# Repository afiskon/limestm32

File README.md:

# limestm32
LimeSTM32: open development board based on STM32F405/STM32F415

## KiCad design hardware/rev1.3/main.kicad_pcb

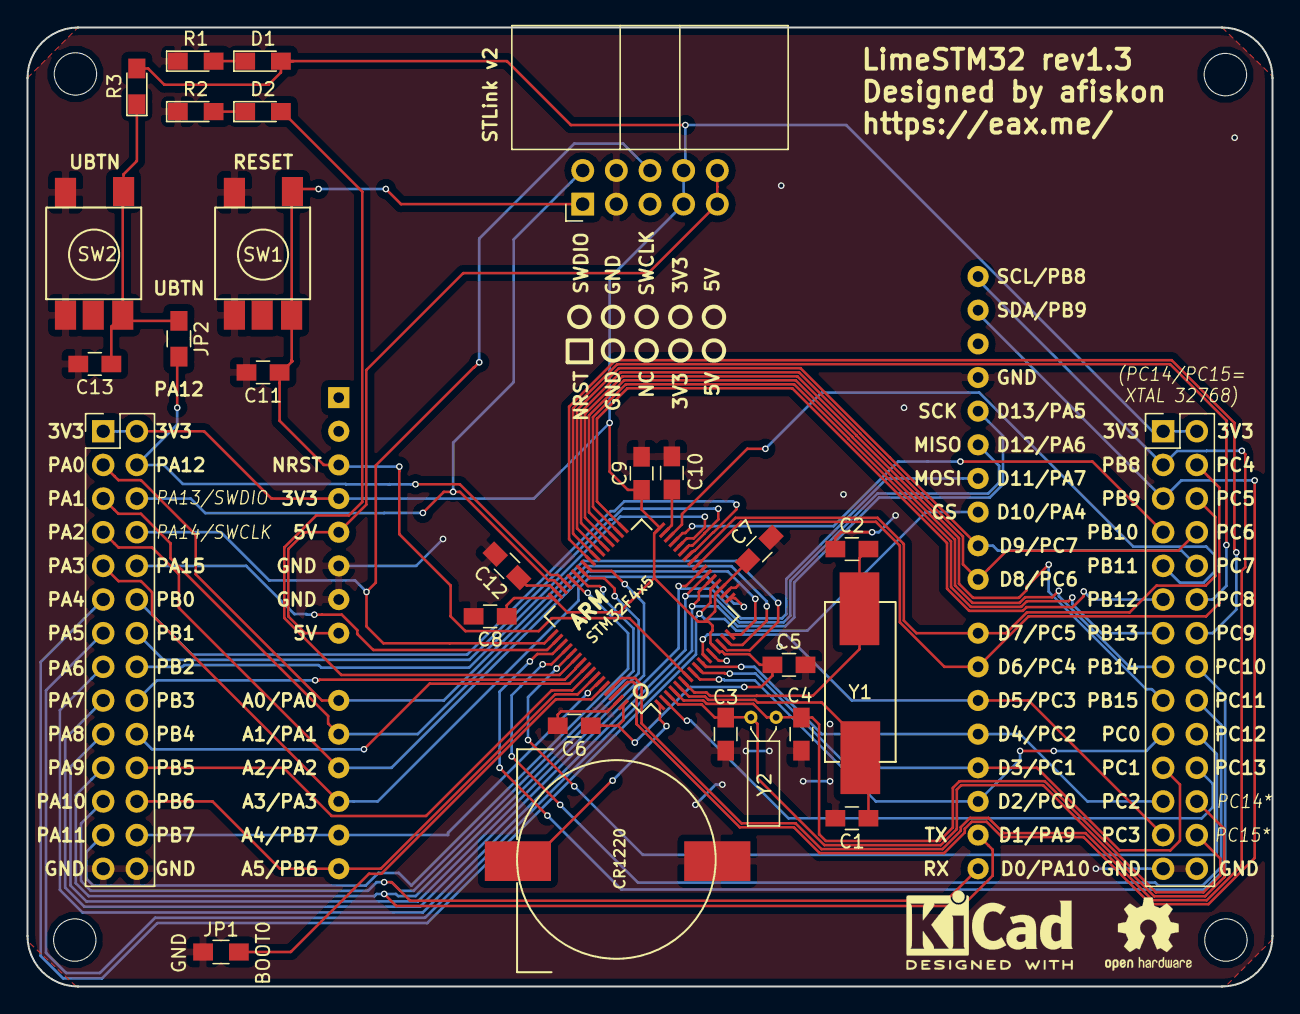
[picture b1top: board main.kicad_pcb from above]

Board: 2 copper layers, 94.0 x 72.4 mm, 36 parts (1 on the bottom side), 62 nets.

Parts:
BT1: Battery_Cell; CR1220_Battery_Holder
C1, C2: 22 pF; C_0805_HandSoldering
C3, C4: 10 pF; C_0805_HandSoldering
C5, C6, C7, C8, C9, C11, C13: 0.1; C_0805_HandSoldering
C10, C12: 2.2; C_0805_HandSoldering
D1, D2: LED; LED_0805_HandSoldering
J1: Conn_02x05_Odd_Even; IDC-Header_2x05_Pitch2.54mm_Angled
J2: Arduino_UNO_R3; Arduino_UNO_R3_Only_Pins
J3, J4: Conn_02x14_Top_Bottom; Pin_Header_Straight_2x14_Pitch2.54mm
JP1, JP2: Jumper; R_0805_HandSoldering
MK1, MK2, MK3, MK4: Mounting_Hole; MountingHole_3.2mm_M3
R1, R2: 680; LED_0805_HandSoldering
R3: 10K; LED_0805_HandSoldering
SW1, SW2: SW_Push; Button_SMD_4pins
SYM1: Logo_Open_Hardware_Small; OSHW-Logo2_7.3x6mm_SilkScreen
SYM2: Logo_Open_Hardware_Small; KiCad-Logo2_6mm_SilkScreen
U1: STM32F405RGTx; LQFP-64_10x10mm_Pitch0.5mm
Y1: 16 MHz; Crystal_Oscillator_SMD
Y2: 32768; Crystal_DS26_d2.0mm_l6.0mm_Horizontal

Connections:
+3V3: C5.1, C6.1, C7.1, C8.1, C9.1, D1.2, J1.7, J1.8, J2.4, J3.1, J3.2, J4.1, J4.2, R3.2, U1.13, U1.19, U1.32, U1.48, U1.64
+5V: J1.9, J1.10, J2.5, J2.8
GND: BT1.2, C1.2, C2.2, C3.2, C4.2, C5.2, C6.2, C7.2, C8.2, C9.2, C10.2, C11.2, C12.2, C13.2, J1.3, J1.4, J2.6, J2.7, J2.29, J3.27, J3.28, J4.27, J4.28, JP1.1, R1.1, R2.1, SW1.1, SW2.1, U1.12, U1.18, U1.63
NRST: C11.1, J1.1, J2.3, SW1.2, U1.7
unnamed: C10.1, U1.31
unnamed: C12.1, U1.47
unnamed: C13.1, JP2.1, R3.1, SW2.2
unnamed: D1.1, R1.2
unnamed: D2.1, R2.2
unnamed: JP1.2, U1.60
PA0: J2.9, J3.3, U1.14
PA1: J2.10, J3.5, U1.15
PA2: J2.11, J3.7, U1.16
PA3: J2.12, J3.9, U1.17
PA4: J2.25, J3.11, U1.20
PA5: J2.28, J3.13, U1.21
PA6: J2.27, J3.15, U1.22
PA7: J2.26, J3.17, U1.23
PA8: J3.19, U1.41
PA9: J2.16, J3.21, U1.42
PA10: J2.15, J3.23, U1.43
PA11: J3.25, U1.44
PA12: J3.4, JP2.2, U1.45
PA13: J1.2, J3.6, U1.46
PA14: J1.6, J3.8, U1.49
PA15: J3.10, U1.50
PB0: J3.12, U1.26
PB1: J3.14, U1.27
PB2: J3.16, U1.28
PB3: J3.18, U1.55
PB4: J3.20, U1.56
PB5: J3.22, U1.57
PB6: J2.14, J3.24, U1.58
PB7: J2.13, J3.26, U1.59
PB8: J2.32, J4.3, U1.61
PB9: J2.31, J4.5, U1.62
PB10: J4.7, U1.29
PB11: J4.9, U1.30
PB12: J4.11, U1.33
PB13: J4.13, U1.34
PB14: J4.15, U1.35
PB15: J4.17, U1.36
PC0: J2.17, J4.19, U1.8
PC1: J2.18, J4.21, U1.9
PC2: J2.19, J4.23, U1.10
PC3: J2.20, J4.25, U1.11
PC4: J2.21, J4.4, U1.24
PC5: J2.22, J4.6, U1.25
PC6: J2.23, J4.8, U1.37
PC7: J2.24, J4.10, U1.38
PC8: J4.12, U1.39
PC9: J4.14, U1.40
PC10: J4.16, U1.51
PC11: J4.18, U1.52
PC12: J4.20, U1.53
PC13: J4.22, U1.2
PC14: C3.1, J4.24, U1.3, Y2.1
PC15: C4.1, J4.26, U1.4, Y2.2
PD2: D2.2, U1.54
PH0: C1.1, U1.5, Y1.1
PH1: C2.1, U1.6, Y1.2
VBAT: BT1.1, U1.1

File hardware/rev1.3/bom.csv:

Reference, Quantity, Value, Footprint, Datasheet
BT1 ,1,"Battery_Cell","My_Library:CR1220_Battery_Holder",""
C10 C12 ,2,"2.2","Capacitors_SMD:C_0805_HandSoldering",""
C1 C2 ,2,"22 pF","Capacitors_SMD:C_0805_HandSoldering",""
C3 C4 ,2,"10 pF","Capacitors_SMD:C_0805_HandSoldering",""
C11 C13 C5 C6 C7 C8 C9 ,7,"0.1","Capacitors_SMD:C_0805_HandSoldering",""
D1 D2 ,2,"LED","LEDs:LED_0805_HandSoldering",""
J1 ,1,"Conn_02x05_Odd_Even","Connectors_IDC:IDC-Header_2x05_Pitch2.54mm_Angled",""
J2 ,1,"Arduino_UNO_R3","My_Library:Arduino_UNO_R3_Only_Pins","https://www.arduino.cc/en/Main/arduinoBoardUno"
J3 J4 ,2,"Conn_02x14_Top_Bottom","Pin_Headers:Pin_Header_Straight_2x14_Pitch2.54mm",""
JP1 JP2 ,2,"Jumper","Resistors_SMD:R_0805_HandSoldering",""
MK1 MK2 MK3 MK4 ,4,"Mounting_Hole","Mounting_Holes:MountingHole_3.2mm_M3",""
R1 R2 ,2,"680","LEDs:LED_0805_HandSoldering",""
R3 ,1,"10K","LEDs:LED_0805_HandSoldering",""
SW1 SW2 ,2,"FSM1LP","My_Library:Button_SMD_4pins",""
SYM1 ,1,"Logo_Open_Hardware_Small","Symbols:OSHW-Logo2_7.3x6mm_SilkScreen",""
SYM2 ,1,"Logo_Open_Hardware_Small","Symbols:KiCad-Logo2_6mm_SilkScreen",""
U1 ,1,"STM32F405RGTx","Housings_QFP:LQFP-64_10x10mm_Pitch0.5mm","http://www.st.com/st-web-ui/static/active/en/resource/techni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"
Y1 ,1,"16 MHz","My_Library:Crystal_Oscillator_SMD",""
Y2 ,1,"32768","Crystals:Crystal_DS26_d2.0mm_l6.0mm_Horizontal",""

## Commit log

2018-08-01 Code moved from a sandbox repository
2018-08-01 Add Gerber files
2019-10-24 Upgrade to KiCad 5.1.x
2020-09-15 Get rid README copy from other project that was used as a template
